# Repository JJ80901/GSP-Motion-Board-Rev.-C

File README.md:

# GSP Wireless Motion Board Rev. C
**Wireless motion board for senior design at Missouri S&amp;T**

This board is designed to capture and wirelessly transmit motion data during a frisbee toss. It features an ESP32-C3-Mini-N4 microcontroller for efficient Bluetooth Low Energy (BLE) communication and an ICM-42670 high-precision 6DOF IMU for real-time motion tracking.

The primary goal of this project is to analyze key motion parameters of a frisbee throw, including initial spin rate (RPM), launch angle, stability, and acceleration. The ICM-42670 provides high-resolution accelerometer and gyroscope data, which allows for precise measurement of motion dynamics.

This design improves upon previous iterations by optimizing power efficiency and reducing form factor for future iterations. The onboard TLV62569DBVT switching regulator ensures stable power delivery to both the ESP32 and IMU. The compact size and BLE connectivity make this an ideal prototype for real-world frisbee motion analysis, with potential applications in sports analytics, biomechanics research, and performance optimization.

Schematic design by Josue Cavazos and Andrew Thomas

PCB Design led by Josue Cavazos

---

### What you'll find in this repository:
- Hardware designs (made in KiCad)
- Reference designs
- Device datasheets
- Circuit simulations

---

### Repository Project Structure:
- *3D Models* - Models for PCB components not found in the standard KiCad library
- *BOM* - An interactive HTML bill of materials (generated from the *Interactive HTML BOM* Plugin)
- *Datasheets* - Datasheets for specific devices used, such as the buck converter, transistors, battery charger, etc.
- *Docs* - Reference schematics used in the circuit design phase
- *Images* - High quality renderings of the final PCB in 3D
- *Libraries* - Folders to include schematic symbols and footprints for components not found in the standard KiCad library
- *Schematics* - PDFs of entire PCB schematic
- *Simulations* - LTSpice simulation block with any custom component libraries
- KiCad hardware design files

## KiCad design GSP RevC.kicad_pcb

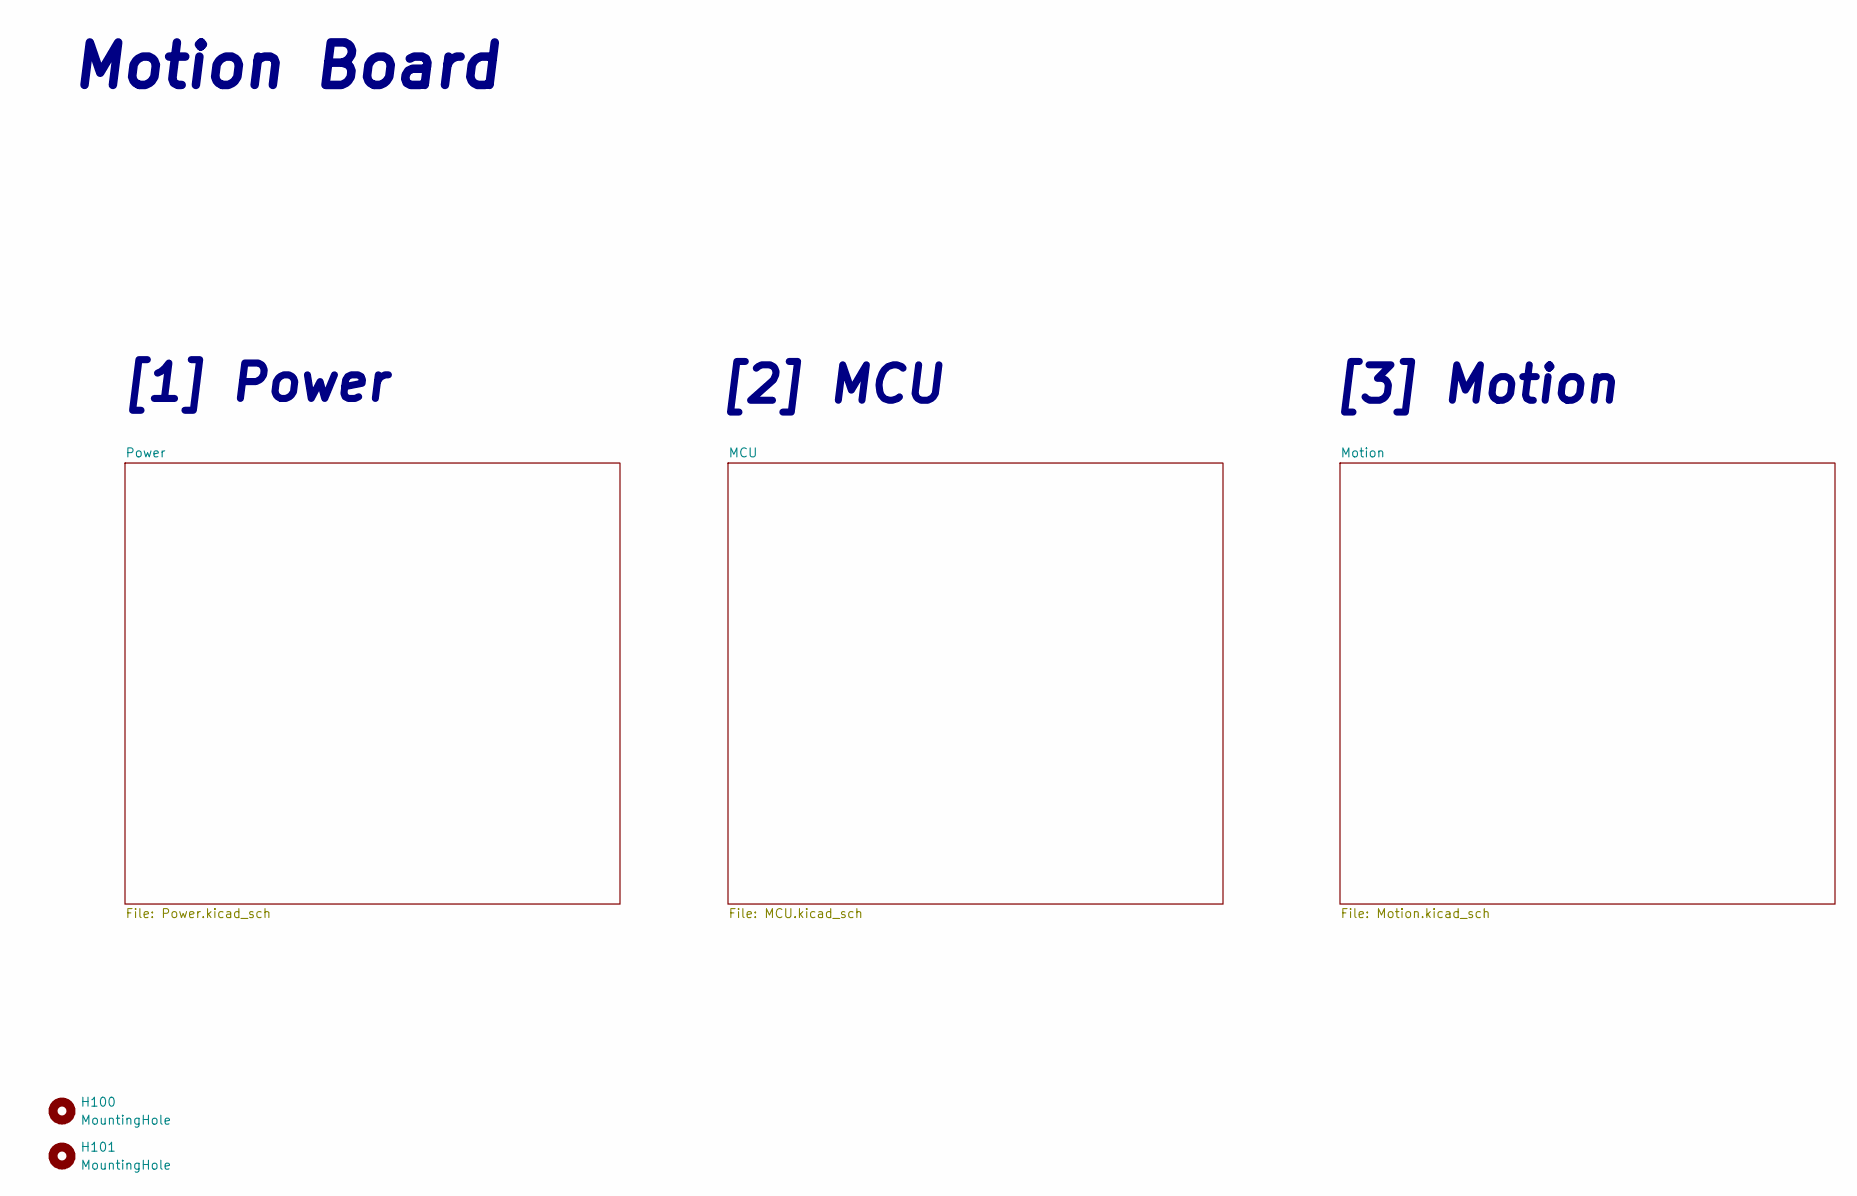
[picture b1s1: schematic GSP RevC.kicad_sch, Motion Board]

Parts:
H100, H101: MountingHole; MountingHole_2.2mm_M2

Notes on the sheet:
[2] MCU
[3] Motion
Motion Board
[1] Power

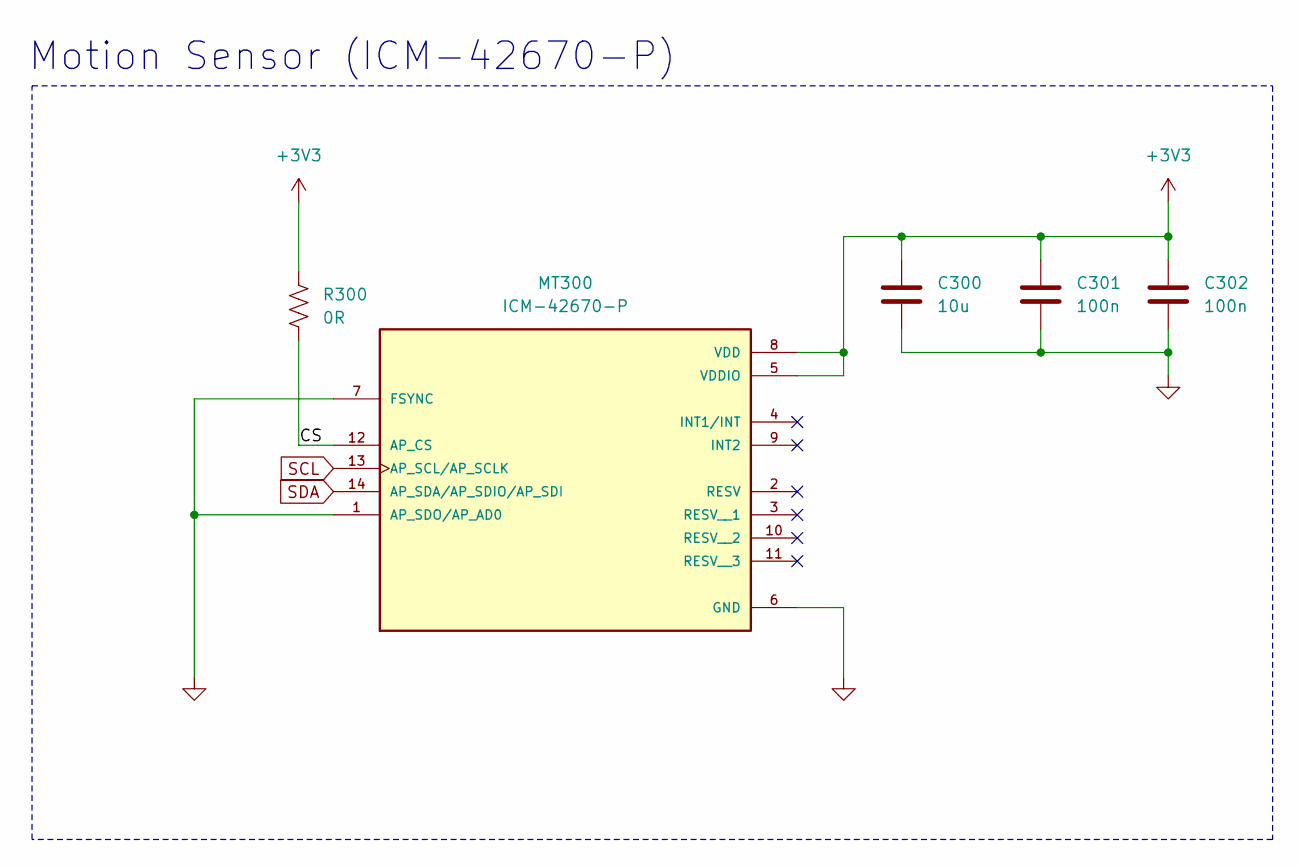
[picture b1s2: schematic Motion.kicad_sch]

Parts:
C300: 10u; C_0603_1608Metric_Pad1.08x0.95mm_HandSolder
C301, C302: 100n; C_0603_1608Metric_Pad1.08x0.95mm_HandSolder
MT300: ICM-42670-P; XDCR_ICM-42670-P; PARTREV 1.1
R300: 0R; R_0603_1608Metric_Pad0.98x0.95mm_HandSolder

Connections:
+3V3: C300.1, C301.1, C302.1, MT300.5 (VDDIO), MT300.8 (VDD), R300.1; also elsewhere on the board
/Motion/CS: MT300.12 (AP_CS), R300.2
GND: C300.2, C301.2, C302.2, MT300.1 (AP_SDO/AP_AD0), MT300.6 (GND), MT300.7 (FSYNC); also elsewhere on the board
SCL: MT300.13 (AP_SCL/AP_SCLK); also elsewhere on the board
SDA: MT300.14 (AP_SDA/AP_SDIO/AP_SDI); also elsewhere on the board

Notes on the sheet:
Motion Sensor (ICM-42670-P)

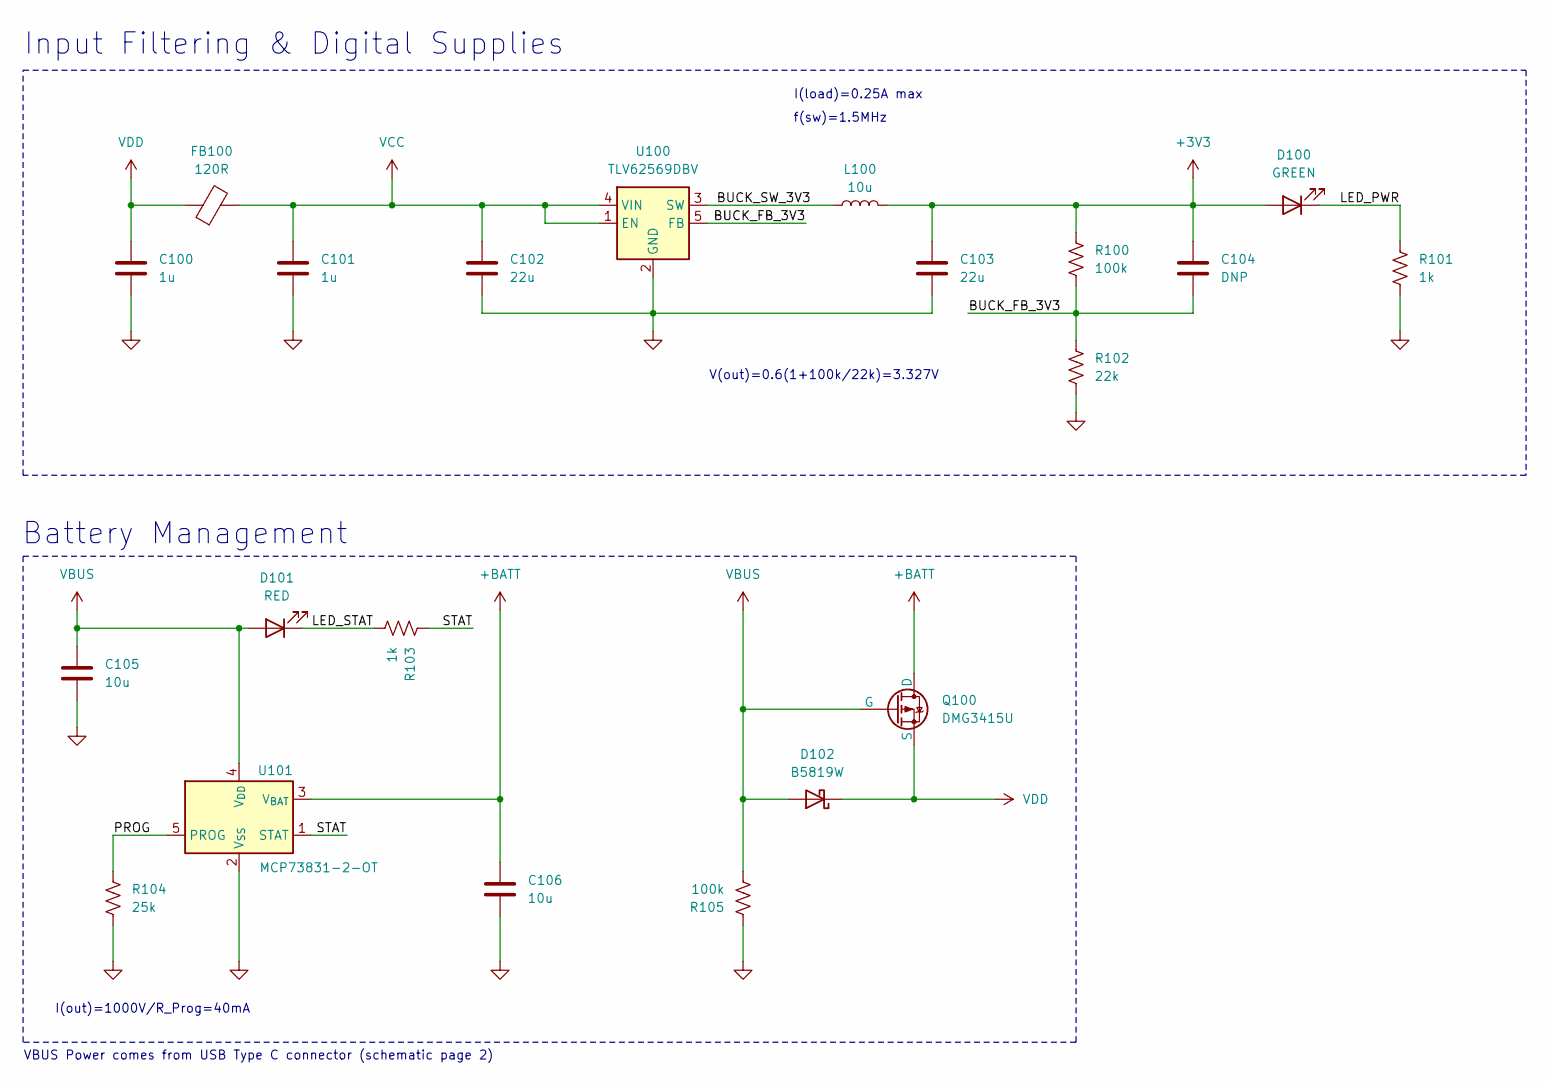
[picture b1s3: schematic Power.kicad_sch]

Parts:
C100, C101: 1u; C_0603_1608Metric_Pad1.08x0.95mm_HandSolder
C102, C103: 22u; C_0805_2012Metric_Pad1.18x1.45mm_HandSolder
C104: DNP; C_0603_1608Metric_Pad1.08x0.95mm_HandSolder
C105, C106: 10u; C_0603_1608Metric_Pad1.08x0.95mm_HandSolder
D100: GREEN; LED_0603_1608Metric_Pad1.05x0.95mm_HandSolder
D101: RED; LED_0603_1608Metric_Pad1.05x0.95mm_HandSolder
D102: B5819W; D_SOD-123
FB100: 120R; L_0603_1608Metric_Pad1.05x0.95mm_HandSolder
L100: 10u; IND_VLS4015CX-100M-H
Q100: DMG3415U; SOT-23
R100, R105: 100k; R_0603_1608Metric_Pad0.98x0.95mm_HandSolder
R101, R103: 1k; R_0603_1608Metric_Pad0.98x0.95mm_HandSolder
R102: 22k; R_0603_1608Metric_Pad0.98x0.95mm_HandSolder
R104: 25k; R_0603_1608Metric_Pad0.98x0.95mm_HandSolder
U100: TLV62569DBV; SOT-23-5
U101: MCP73831-2-OT; SOT-23-5

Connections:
+3V3: C103.1, C104.1, D100.2 (A), L100.2, R100.1; also elsewhere on the board
+BATT: C106.1, Q100.1 (D), U101.3 (V_{BAT}); also elsewhere on the board
/Power/BUCK_FB_3V3: C104.2, R100.2, R102.1, U100.5 (FB)
/Power/BUCK_SW_3V3: L100.1, U100.3 (SW)
/Power/LED_PWR: D100.1 (K), R101.1
/Power/LED_STAT: D101.1 (K), R103.2
/Power/PROG: R104.1, U101.5 (PROG)
/Power/STAT: R103.1, U101.1 (STAT)
GND: C100.2, C101.2, C102.2, C103.2, C105.2, C106.2, R101.2, R102.2, R104.2, R105.1, U100.2 (GND), U101.2 (V_{SS}); also elsewhere on the board
VBUS: C105.1, D101.2 (A), D102.2 (A), Q100.2 (G), R105.2, U101.4 (V_{DD}); also elsewhere on the board
VCC: C101.1, C102.1, FB100.2, U100.1 (EN), U100.4 (VIN)
VDD: C100.1, D102.1 (K), FB100.1, Q100.3 (S)

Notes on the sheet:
Battery Management
VBUS Power comes from USB Type C connector (schematic page 2)
V(out)=0.6(1+100k/22k)=3.327V
Input Filtering & Digital Supplies
I(load)=0.25A max
I(out)=1000V/R_Prog=40mA
f(sw)=1.5MHz

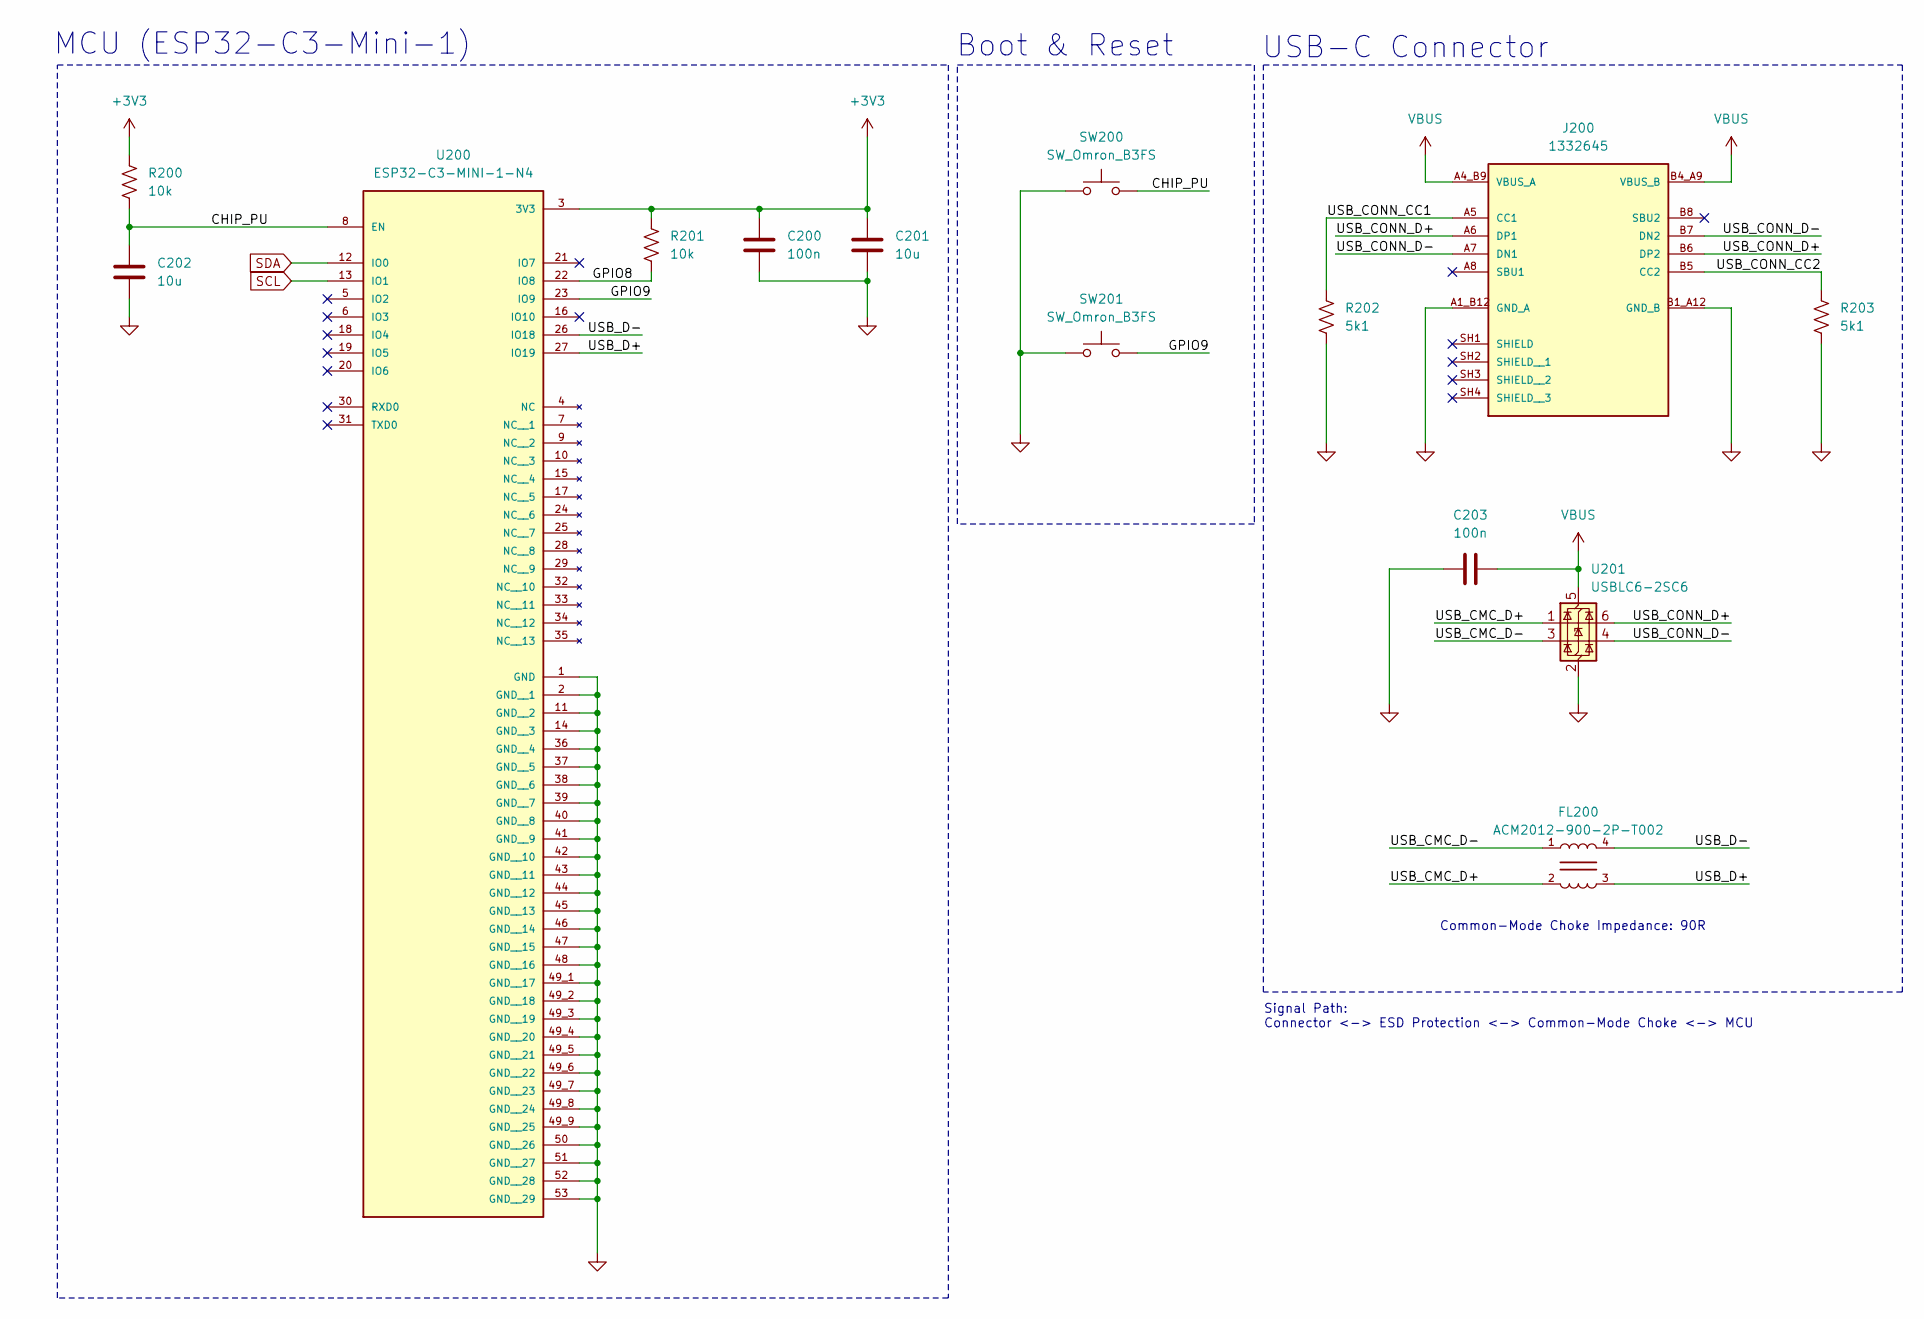
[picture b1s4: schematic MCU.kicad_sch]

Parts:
C200, C203: 100n; C_0603_1608Metric_Pad1.08x0.95mm_HandSolder
C201, C202: 10u; C_0603_1608Metric_Pad1.08x0.95mm_HandSolder
FL200: ACM2012-900-2P-T002; FIL_ACM2012-900-2P-T002
J200: 1332645; PHOENIX_1332645; PARTREV 17.01.2022
R200, R201: 10k; R_0603_1608Metric_Pad0.98x0.95mm_HandSolder
R202, R203: 5k1; R_0603_1608Metric_Pad0.98x0.95mm_HandSolder
SW200, SW201: SW_Omron_B3FS; SW_PUSH_6mm
U200: ESP32-C3-MINI-1-N4; XCVR_ESP32-C3-MINI-1-N4; PARTREV v1.0
U201: USBLC6-2SC6; SOT-23-6

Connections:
+3V3: C200.1, C201.1, R200.1, R201.1, U200.3 (3V3); also elsewhere on the board
/MCU/CHIP_PU: C202.1, R200.2, SW200.2, U200.8 (EN)
/MCU/GPIO8: R201.2, U200.22 (IO8)
/MCU/GPIO9: SW201.2, U200.23 (IO9)
/MCU/USB_CMC_D+: FL200.2, U201.1 (I/O1)
/MCU/USB_CMC_D-: FL200.1, U201.3 (I/O2)
/MCU/USB_CONN_CC1: J200.A5 (CC1), R202.1
/MCU/USB_CONN_CC2: J200.B5 (CC2), R203.1
/MCU/USB_CONN_D+: J200.A6 (DP1), J200.B6 (DP2), U201.6 (I/O1)
/MCU/USB_CONN_D-: J200.A7 (DN1), J200.B7 (DN2), U201.4 (I/O2)
/MCU/USB_D+: FL200.3, U200.27 (IO19)
/MCU/USB_D-: FL200.4, U200.26 (IO18)
GND: C200.2, C201.2, C202.2, C203.2, J200.A1_B12 (GND_A), J200.B1_A12 (GND_B), R202.2, R203.2, SW200.1, SW201.1, U200.1 (GND), U200.2 (GND__1), U200.11 (GND__2), U200.14 (GND__3), U200.36 (GND__4), U200.37 (GND__5), U200.38 (GND__6), U200.39 (GND__7), U200.40 (GND__8), U200.41 (GND__9), U200.42 (GND__10), U200.43 (GND__11), U200.44 (GND__12), U200.45 (GND__13), U200.46 (GND__14), U200.47 (GND__15), U200.48 (GND__16), U200.49_1 (GND__17), U200.49_2 (GND__18), U200.49_3 (GND__19), U200.49_4 (GND__20), U200.49_5 (GND__21), U200.49_6 (GND__22), U200.49_7 (GND__23), U200.49_8 (GND__24), U200.49_9 (GND__25), U200.50 (GND__26), U200.51 (GND__27), U200.52 (GND__28), U200.53 (GND__29), U201.2 (GND); also elsewhere on the board
SCL: U200.13 (IO1); also elsewhere on the board
SDA: U200.12 (IO0); also elsewhere on the board
VBUS: C203.1, J200.A4_B9 (VBUS_A), J200.B4_A9 (VBUS_B), U201.5 (VBUS); also elsewhere on the board

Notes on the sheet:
Signal Path: Connector <-> ESD Protection <-> Common-Mode Choke <-> MCU
USB-C Connector
Common-Mode Choke Impedance: 90R
Boot & Reset
MCU (ESP32-C3-Mini-1)

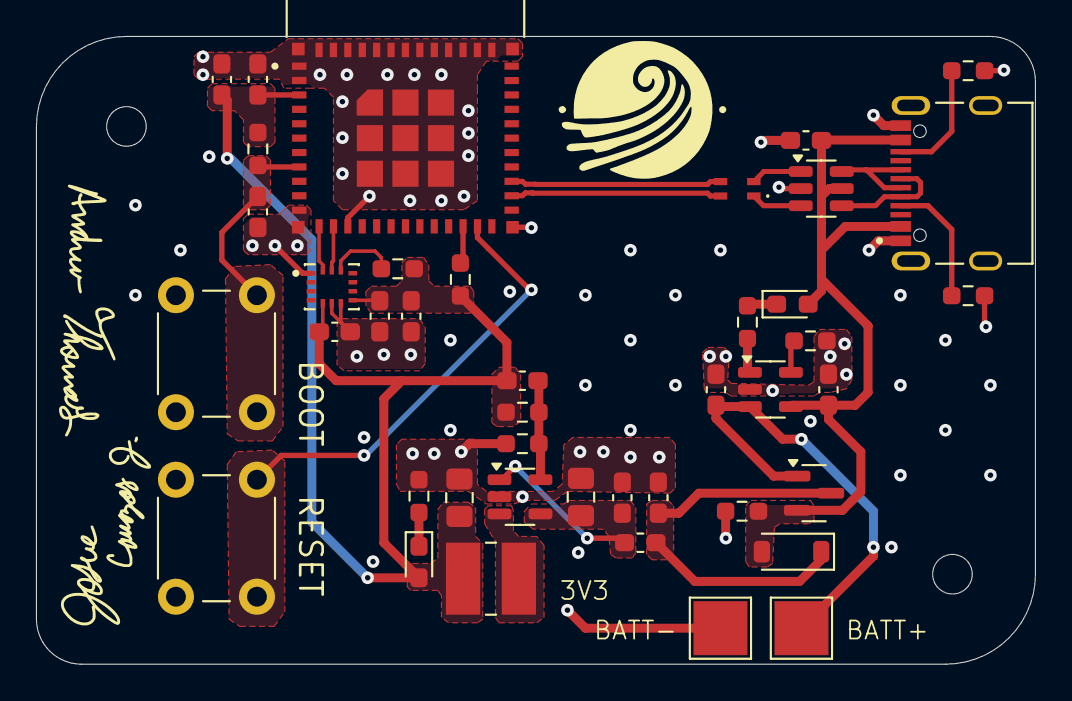
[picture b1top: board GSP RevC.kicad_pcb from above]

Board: 4 copper layers, 55.5 x 34.9 mm, 44 parts (0 on the bottom side), 26 nets.

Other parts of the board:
TP200: Battery+; TestPoint_Pad_3.0x3.0mm
TP201: Battery-; TestPoint_Pad_3.0x3.0mm

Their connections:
+BATT: TP200.1; also elsewhere on the board
GND: TP201.1; also elsewhere on the board

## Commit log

2025-02-24 Testing readme update
2025-02-24 Last test
2025-02-24 Polished README
2025-02-24 Fixed revision letter in README
